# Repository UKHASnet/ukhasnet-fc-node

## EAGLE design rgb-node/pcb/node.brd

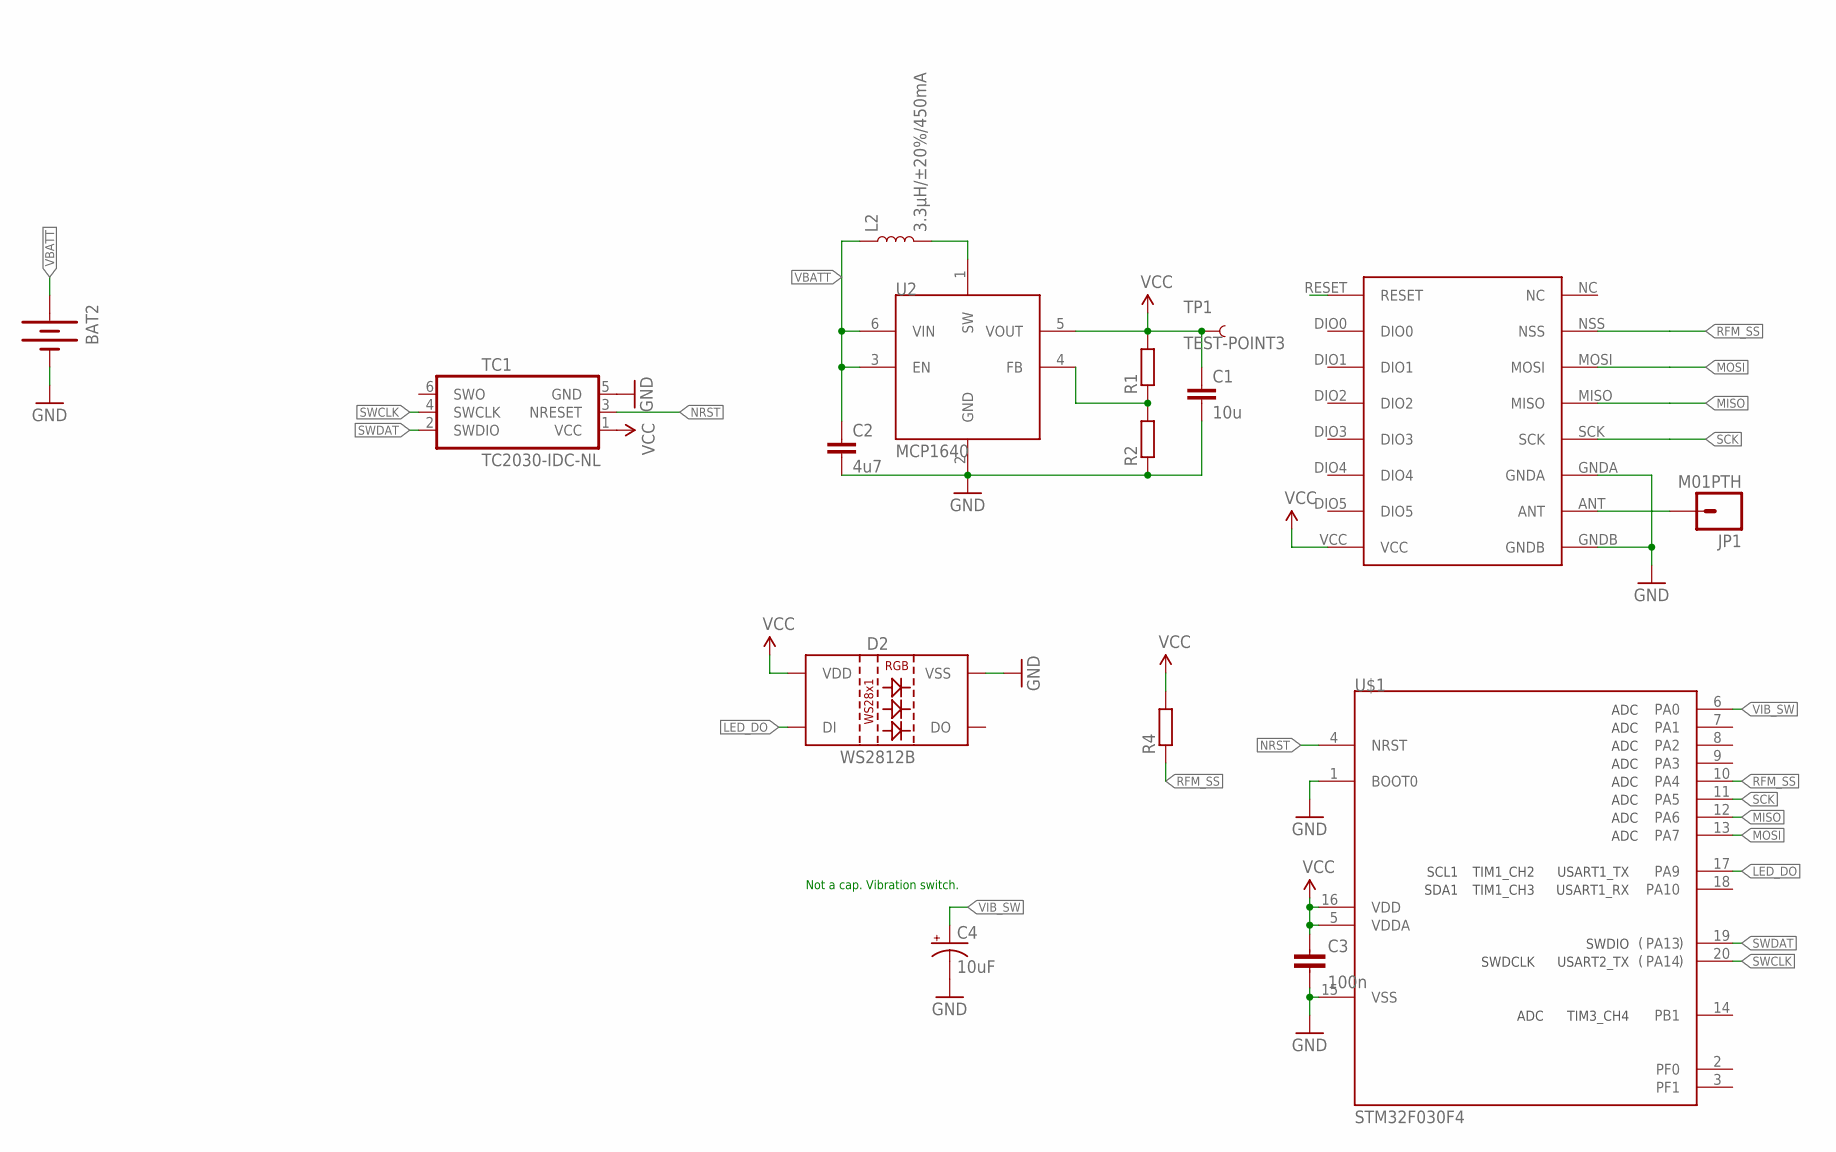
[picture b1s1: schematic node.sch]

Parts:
BAT2: BATTERYAA; BATTERY-AA
C1: 10u; C0603
C2: 4u7; C0603
C3: 100n; C0603-N
C4: 10uF; CPOL-RADIAL-2.5MM-5MM
D2: WS2812B
JP1: M01PTH; 1X01
L2: 3.3µH/±20%/450mA; 0805
R1, R2, R4: R-EU_R0603; R0603
TC1: TC2030-IDC-NL
TP1: TEST-POINT3; PAD.03X.03
U2: MCP1640; SOT23-6
U$1: STM32F030F4; TSSOP20
U$4: RFM69HW; RFM

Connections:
GND: BAT2.GND@1 (-), C1.2, C2.2, C3.2, C4.2 (-), D2.3 (VSS), R2.1, TC1.5 (GND), U2.2 (GND), U$1.1 (BOOT0), U$1.15 (VSS), U$4.GNDA, U$4.GNDB
LED_DO: D2.4 (DI), U$1.17 (PA9)
MISO: U$1.12 (PA6), U$4.MISO
MOSI: U$1.13 (PA7), U$4.MOSI
unnamed: L2.2, U2.1 (SW)
unnamed: R1.1, R2.2, U2.4 (FB)
unnamed: JP1.1, U$4.ANT
NRST: TC1.3 (NRESET), U$1.4 (NRST)
RFM_SS: R4.1, U$1.10 (PA4), U$4.NSS
SCK: U$1.11 (PA5), U$4.SCK
SWCLK: TC1.4 (SWCLK), U$1.20 (PA14)
SWDAT: TC1.2 (SWDIO), U$1.19 (PA13)
VBATT: BAT2.PWR@1 (+), C2.1, L2.1, U2.3 (EN), U2.6 (VIN)
VCC: C1.1, C3.1, D2.1 (VDD), R1.2, R4.2, TC1.1 (VCC), TP1.P$1, U2.5 (VOUT), U$1.5 (VDDA), U$1.16 (VDD), U$4.VCC
VIB_SW: C4.1 (+), U$1.6 (PA0)

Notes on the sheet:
Not a cap. Vibration switch.

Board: 2 copper layers, 16 parts (1 on the bottom side), 15 nets, no tracks yet.

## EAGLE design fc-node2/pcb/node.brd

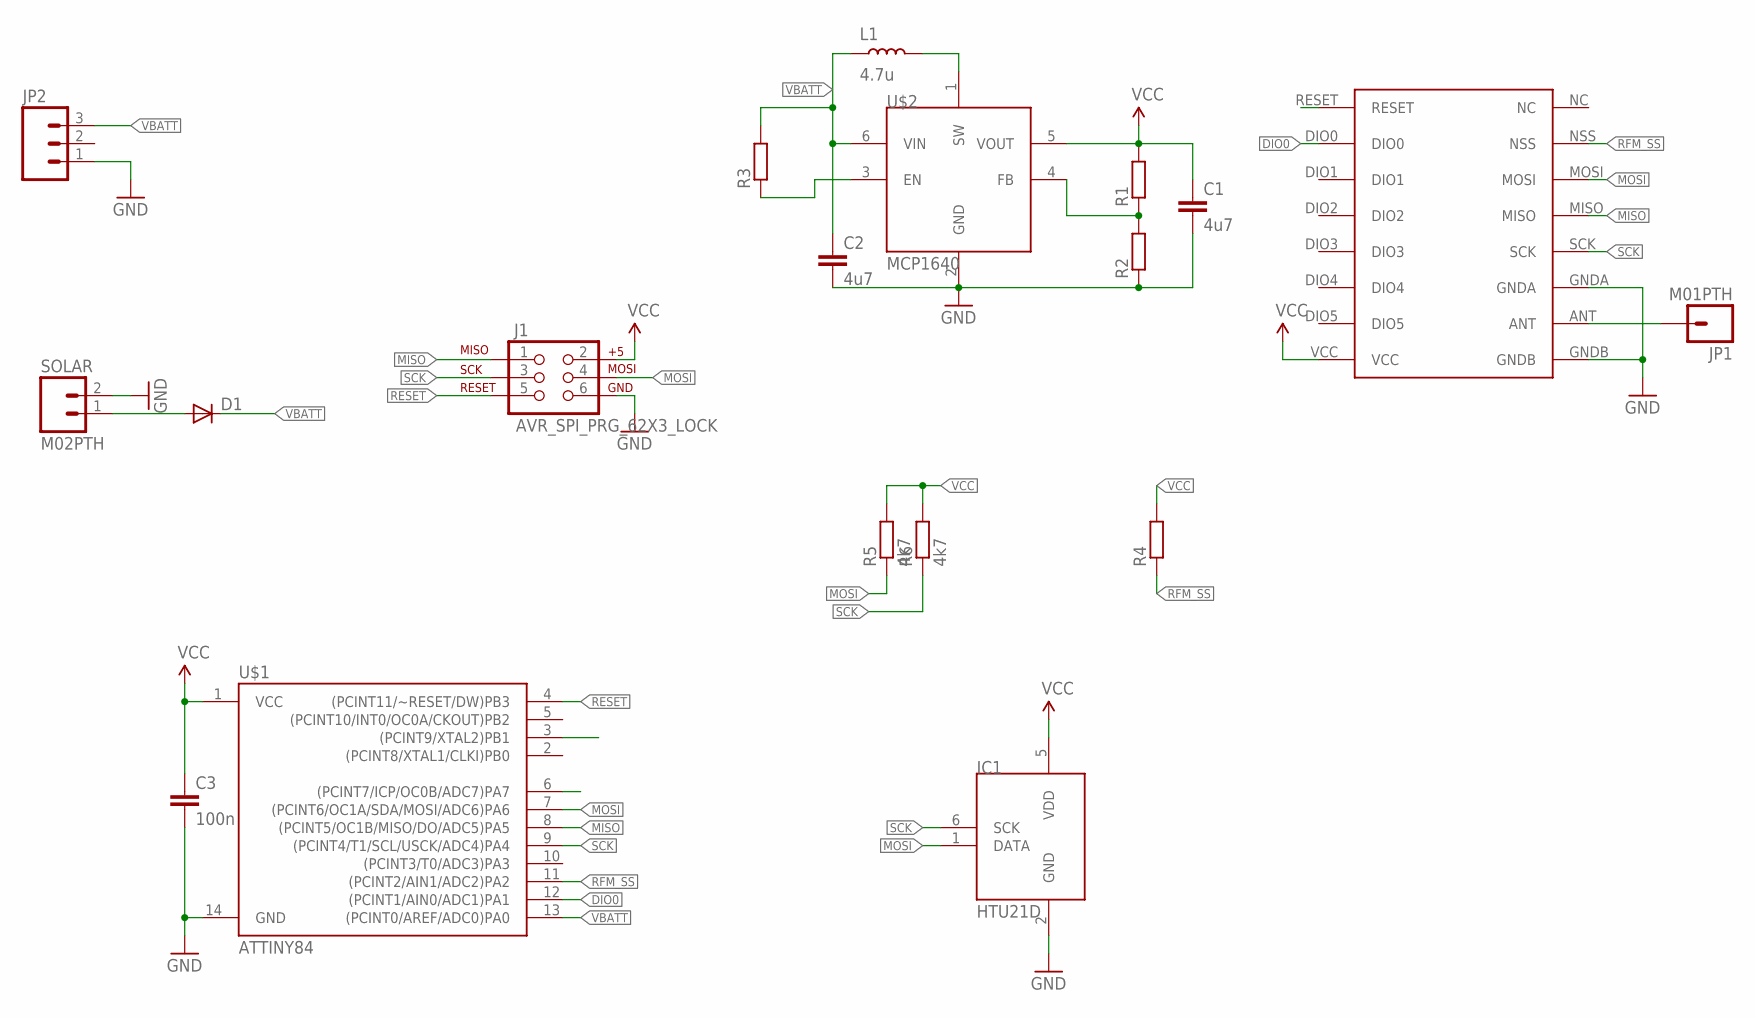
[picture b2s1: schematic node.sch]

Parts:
C1, C2: 4u7; C0603
C3: 100n; C0603
D1: DIODE-SOD123; SOD123
IC1: HTU21D; DFN6-L
J1: AVR_SPI_PRG_62X3_LOCK; 2X3_LOCK
JP1: M01PTH; 1X01
JP2: M03PTH; 1X03
L1: 4.7u; L0603-N
R1, R2, R3, R4: R-EU_R0603; R0603
R5, R6: 4k7; R0603
SOLAR: M02PTH; 1X02
U$1: ATTINY84; SO14
U$2: MCP1640; SOT23-6
U$4: RFM69HW; RFM

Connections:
DIO0: U$1.12 ((PCINT1/AIN0/ADC1)PA1), U$4.DIO0
EN: R3.1, U$2.3 (EN)
GND: C1.2, C2.2, C3.2, IC1.2 (GND), J1.6, JP2.1, R2.1, SOLAR.2, U$1.14 (GND), U$2.2 (GND), U$4.GNDA, U$4.GNDB
MISO: J1.1, U$1.8 ((PCINT5/OC1B/MISO/DO/ADC5)PA5), U$4.MISO
MOSI: IC1.1 (DATA), J1.4, R5.1, U$1.7 ((PCINT6/OC1A/SDA/MOSI/ADC6)PA6), U$4.MOSI
unnamed: L1.2, U$2.1 (SW)
unnamed: R1.1, R2.2, U$2.4 (FB)
unnamed: JP1.1, U$4.ANT
unnamed: D1.A, SOLAR.1
RESET: J1.5, U$1.4 ((PCINT11/~RESET/DW)PB3)
RFM_SS: R4.1, U$1.11 ((PCINT2/AIN1/ADC2)PA2), U$4.NSS
SCK: IC1.6 (SCK), J1.3, R6.1, U$1.9 ((PCINT4/T1/SCL/USCK/ADC4)PA4), U$4.SCK
VBATT: C2.1, D1.C, JP2.3, L1.1, R3.2, U$1.13 ((PCINT0/AREF/ADC0)PA0), U$2.6 (VIN)
VCC: C1.1, C3.1, IC1.5 (VDD), J1.2, R1.2, R4.2, R5.2, R6.2, U$1.1 (VCC), U$2.5 (VOUT), U$4.VCC

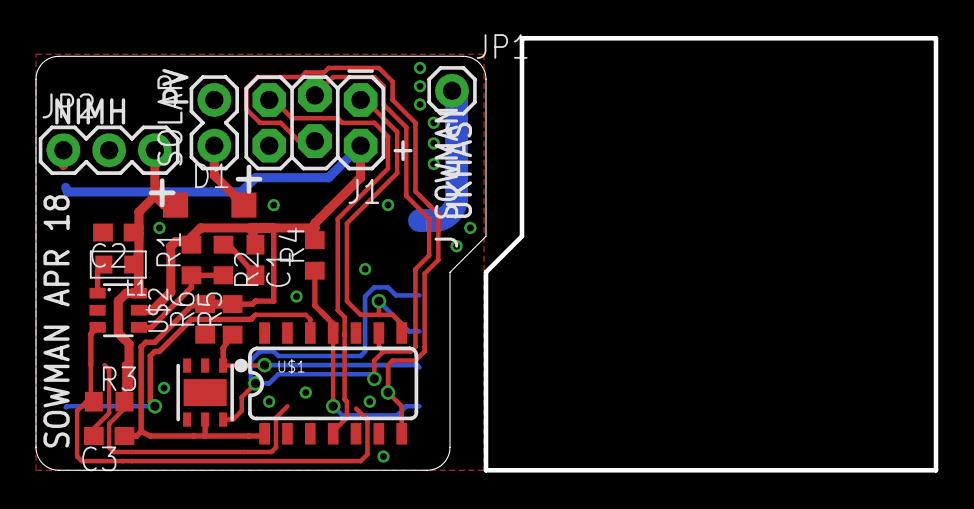
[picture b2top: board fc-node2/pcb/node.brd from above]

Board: 2 copper layers, 49.9 x 24.0 mm, 19 parts (1 on the bottom side), 14 nets.

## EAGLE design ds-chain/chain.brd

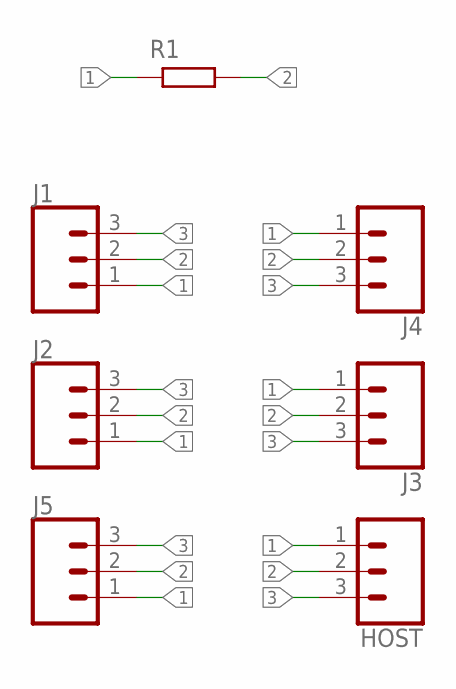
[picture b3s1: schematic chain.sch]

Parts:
HOST: CONN_03LONGPADS; 1X03_LONGPADS
J1, J2, J3, J4, J5: CONN_03LONGPADS; 1X03_LONGPADS
R1: RESISTOR0603-N; R0603-N

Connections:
1: HOST.1, J1.1, J2.1, J3.1, J4.1, J5.1, R1.1
2: HOST.2, J1.2, J2.2, J3.2, J4.2, J5.2, R1.2
3: HOST.3, J1.3, J2.3, J3.3, J4.3, J5.3

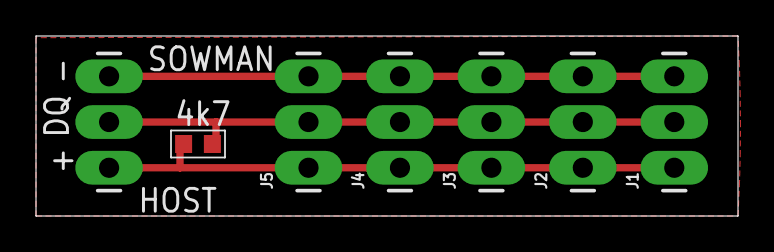
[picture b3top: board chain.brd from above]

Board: 2 copper layers, 39.0 x 10.0 mm, 7 parts (0 on the bottom side), 3 nets.

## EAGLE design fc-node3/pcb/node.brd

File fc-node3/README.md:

ds18b20 library is from
http://davidegironi.blogspot.co.uk/2014/09/a-ds18b20-1-wire-digital-thermometer.html

GPLv3

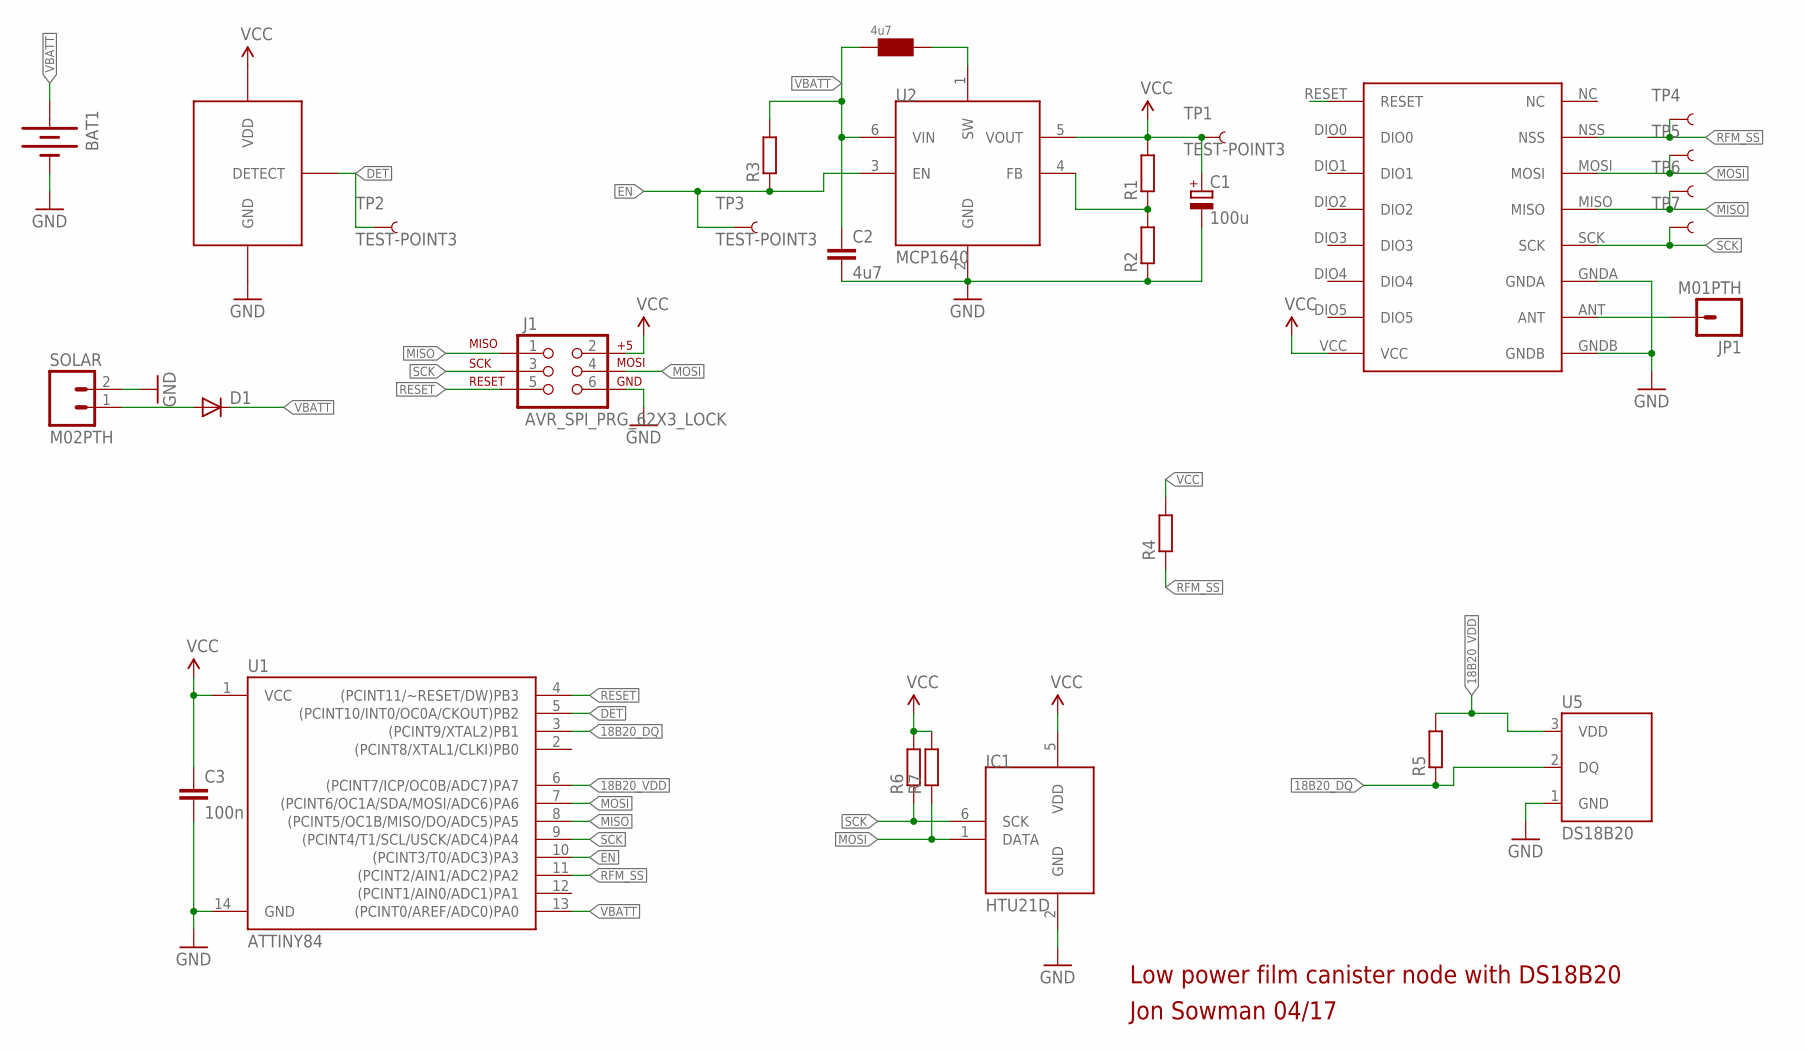
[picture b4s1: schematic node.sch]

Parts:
BAT1: BATTERYAAA; BATTERY-AAA
C1: 100u; SANYO-OSCON_SMD_C6
C2: 4u7; C0603
C3: 100n; C0603
D1: DIODE-SOD123; SOD123
DF: 4u7; BOURNS_SRN5040_L
IC1: HTU21D; DFN6-L
J1: AVR_SPI_PRG_62X3_LOCK; 2X3_LOCK
JP1: M01PTH; 1X01
R1, R2, R3, R4, R5, R6, R7: R-EU_R0603; R0603
SOLAR: M02PTH; 1X02
TP1, TP2, TP3, TP4, TP5, TP6, TP7: TEST-POINT3; PAD.03X.03
U1: ATTINY84; SO14
U2: MCP1640; SOT23-6
U3: BU49X_VDET_SOT235; SOT23-5L
U5: DS18B20; TO-92-AMMO
U$4: RFM69HW; RFM

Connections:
18B20_DQ: R5.1, U1.3 ((PCINT9/XTAL2)PB1), U5.2 (DQ)
18B20_VDD: R5.2, U1.6 ((PCINT7/ICP/OC0B/ADC7)PA7), U5.3 (VDD)
DET: TP2.P$1, U1.5 ((PCINT10/INT0/OC0A/CKOUT)PB2), U3.1 (DETECT)
EN: R3.1, TP3.P$1, U1.10 ((PCINT3/T0/ADC3)PA3), U2.3 (EN)
GND: BAT1.GND@1 (-), C1.-, C2.2, C3.2, IC1.2 (GND), J1.6, R2.1, SOLAR.2, U1.14 (GND), U2.2 (GND), U3.3 (GND), U5.1 (GND), U$4.GNDA, U$4.GNDB
MISO: J1.1, TP6.P$1, U1.8 ((PCINT5/OC1B/MISO/DO/ADC5)PA5), U$4.MISO
MOSI: IC1.1 (DATA), J1.4, R7.1, TP5.P$1, U1.7 ((PCINT6/OC1A/SDA/MOSI/ADC6)PA6), U$4.MOSI
unnamed: DF.P$2, U2.1 (SW)
unnamed: R1.1, R2.2, U2.4 (FB)
unnamed: JP1.1, U$4.ANT
unnamed: D1.A, SOLAR.1
RESET: J1.5, U1.4 ((PCINT11/~RESET/DW)PB3)
RFM_SS: R4.1, TP4.P$1, U1.11 ((PCINT2/AIN1/ADC2)PA2), U$4.NSS
SCK: IC1.6 (SCK), J1.3, R6.1, TP7.P$1, U1.9 ((PCINT4/T1/SCL/USCK/ADC4)PA4), U$4.SCK
VBATT: BAT1.PWR@1 (+), C2.1, D1.C, DF.P$1, R3.2, U1.13 ((PCINT0/AREF/ADC0)PA0), U2.6 (VIN)
VCC: C1.+, C3.1, IC1.5 (VDD), J1.2, R1.2, R4.2, R6.2, R7.2, TP1.P$1, U1.1 (VCC), U2.5 (VOUT), U3.2 (VDD), U$4.VCC

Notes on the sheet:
Low power film canister node with DS18B20
Jon Sowman 04/17

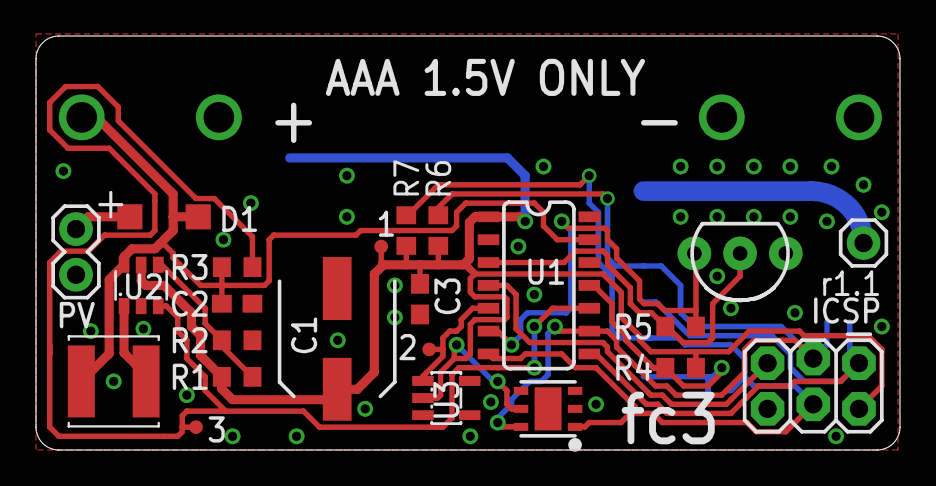
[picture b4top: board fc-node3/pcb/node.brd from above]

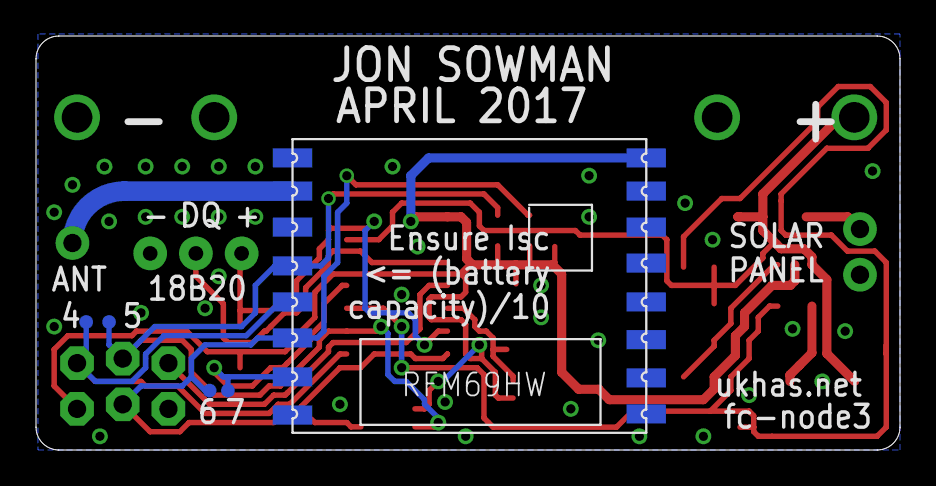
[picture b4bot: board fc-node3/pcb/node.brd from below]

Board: 2 copper layers, 48.0 x 23.0 mm, 29 parts (5 on the bottom side), 16 nets.

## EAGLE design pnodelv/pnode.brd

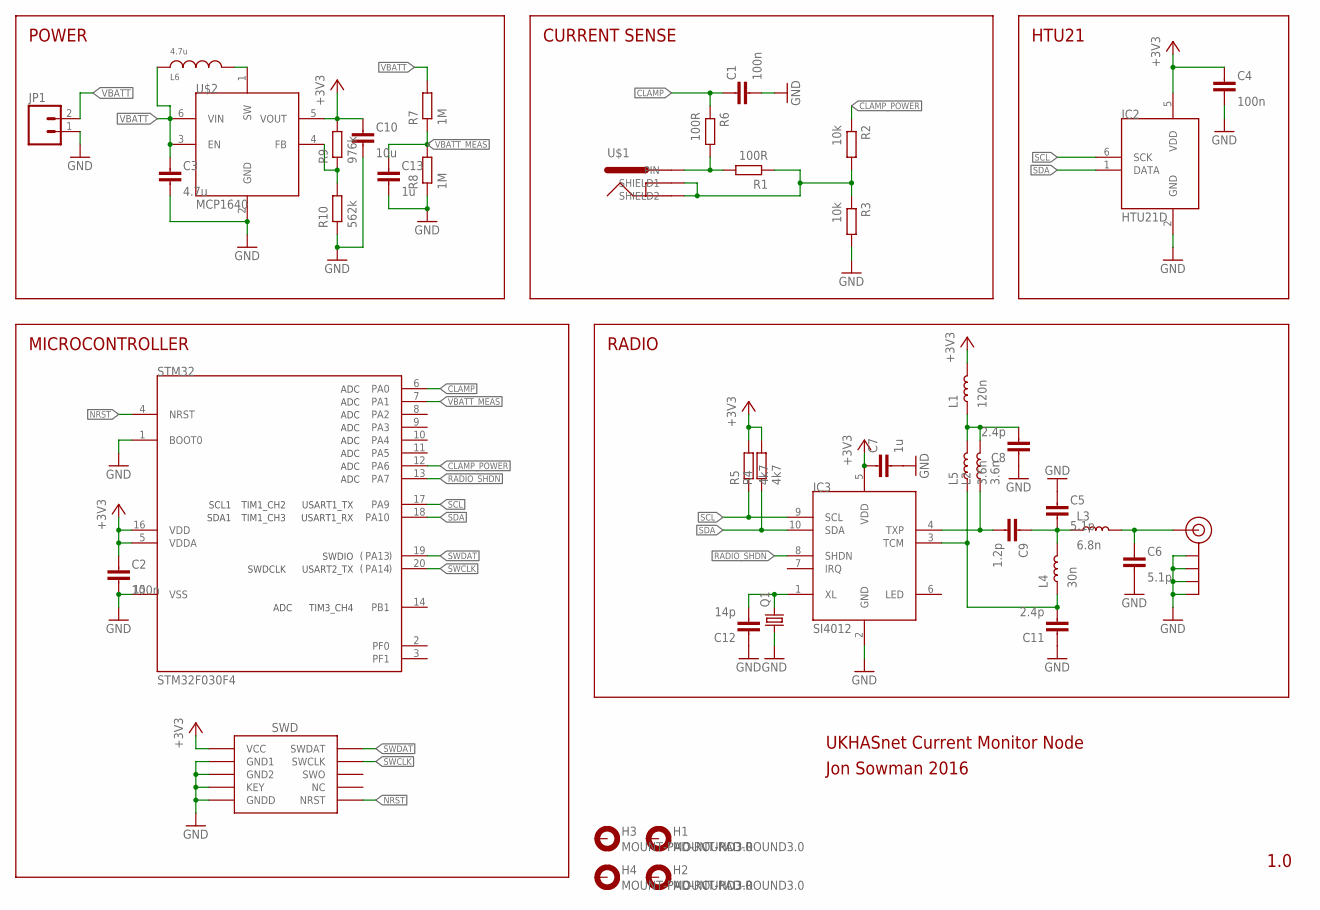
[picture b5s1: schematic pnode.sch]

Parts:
C1, C2, C4: 100n; C0603-N
C3: 4.7u; C0603-N
C5, C6: 5.1p; C0603-N
C7, C13: 1u; C0603-N
C8, C11: 2.4p; C0603-N
C9: 1.2p; C0603-N
C10: 10u; C0603-N
C12: 14p; C0603-N
H1, H2, H3, H4: MOUNT-PAD-ROUND3.0; 3,0-PAD
IC2: HTU21D; DFN6-L
IC3: SI4012; MSOP10
J1: SWD_SHROUD_SMD; SWD_SMD_SHROUD
J$1: SMA_EDGE; SMA-EDGE
JP1: M02PTH; 1X02
L1: 120n; L0603-N
L2, L5: 3.6n; L0402-N
L3: 6.8n; L0402-N
L4: 30n; L0402-N
L6: 4.7u; BOURNS_SDE0403A
Q1: CRYSTALHC49S; HC49/S
R1, R6: 100R; R0603-N
R2, R3: 10k; R0603-N
R4, R5: 4k7; R0603-N
R7, R8: 1M; R0603-N
R9: 976k; R0603-N
R10: 562k; R0603-N
STM32: STM32F030F4; TSSOP20
U$1: 13MM_DC_JACKPTH; 13MM_DC_JACK
U$2: MCP1640; SOT23-6

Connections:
+3V3: C2.1, C4.1, C7.1, C10.1, IC2.5 (VDD), IC3.5 (VDD), J1.1 (VCC), L1.2, R4.2, R5.2, R9.2, STM32.5 (VDDA), STM32.16 (VDD), U$2.5 (VOUT)
CLAMP: C1.1, R6.1, STM32.6 (PA0)
CLAMP_POWER: R2.1, STM32.12 (PA6)
GND: C1.2, C2.2, C3.2, C4.2, C5.1, C6.2, C7.2, C8.1, C10.2, C11.1, C12.1, C13.2, IC2.2 (GND), IC3.2 (GND), J1.3 (GND1), J1.5 (GND2), J1.7 (KEY), J1.9 (GNDD), J$1.GND@0 (GND), J$1.GND@1 (GND), J$1.GND@2 (GND), J$1.GND@3 (GND), JP1.1, Q1.1, R3.2, R8.1, R10.1, STM32.1 (BOOT0), STM32.15 (VSS), U$2.2 (GND)
unnamed: R1.2, R6.2, U$1.1 (PIN)
unnamed: R1.1, R2.2, R3.1, U$1.2 (SHIELD1), U$1.3 (SHIELD2)
unnamed: R9.1, R10.2, U$2.4 (FB)
unnamed: C8.2, L1.1, L2.2, L5.2
unnamed: C12.2, IC3.1 (XL), Q1.2
unnamed: L6.P$2, U$2.1 (SW)
unnamed: C5.2, C9.1, L3.1, L4.2
unnamed: C11.2, IC3.3 (TCM), L4.1, L5.1
unnamed: C9.2, IC3.4 (TXP), L2.1
unnamed: C6.1, J$1.SIG (SIGNAL), L3.2
NRST: J1.10 (NRST), STM32.4 (NRST)
RADIO_SHDN: IC3.8 (SHDN), STM32.13 (PA7)
SCL: IC2.6 (SCK), IC3.9 (SCL), R5.1, STM32.17 (PA9)
SDA: IC2.1 (DATA), IC3.10 (SDA), R4.1, STM32.18 (PA10)
SWCLK: J1.4 (SWCLK), STM32.20 (PA14)
SWDAT: J1.2 (SWDAT), STM32.19 (PA13)
VBATT: C3.1, JP1.2, L6.P$1, R7.2, U$2.3 (EN), U$2.6 (VIN)
VBATT_MEAS: C13.1, R7.1, R8.2, STM32.7 (PA1)

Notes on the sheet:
UKHASnet Current Monitor Node
Jon Sowman 2016
1.0
POWER
CURRENT SENSE
RADIO
MICROCONTROLLER
HTU21

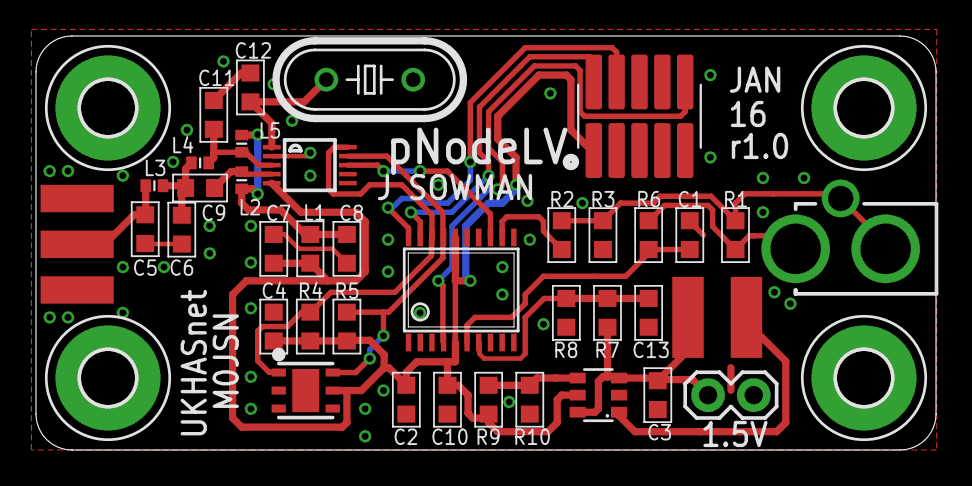
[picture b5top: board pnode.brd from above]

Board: 2 copper layers, 50.0 x 23.0 mm, 42 parts (0 on the bottom side), 22 nets.

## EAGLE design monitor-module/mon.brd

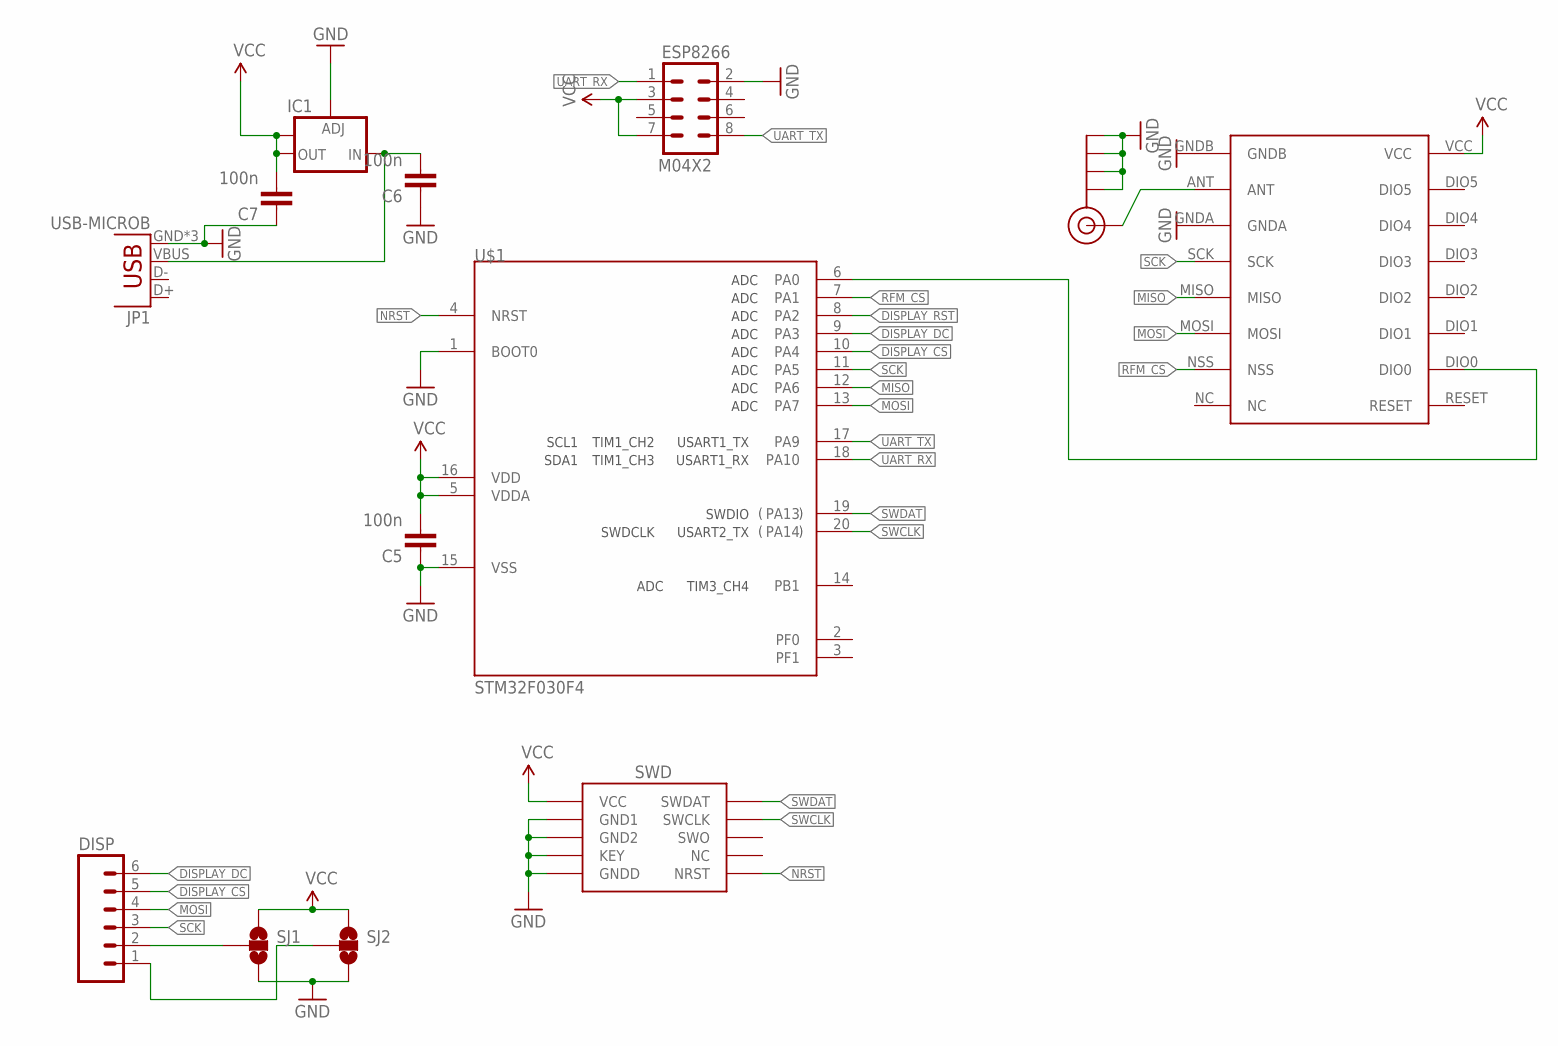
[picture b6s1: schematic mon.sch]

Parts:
C5, C6, C7: 100n; C0603-L
DISP: M06SILK_FEMALE_PTH; 1X06
ESP8266: M04X2; 2X4
IC1: V_REG_LM1117SOT223; SOT223
J$1: SMA_EDGE; SMA-EDGE
JP1: USB-MICROB
SJ1, SJ2: SOLDERJUMPER_2WAYS; SJ_3
U$1: STM32F030F4; TSSOP20
U$2: RFM69HW; RFM
U$4: SWD_SHROUD_SMD; SWD_SMD_SHROUD

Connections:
DISPLAY_CS: DISP.5, U$1.10 (PA4)
DISPLAY_DC: DISP.6, U$1.9 (PA3)
DISPLAY_RST: U$1.8 (PA2)
GND: C5.1, C6.1, C7.1, ESP8266.2, IC1.1 (ADJ), J$1.GND@0 (GND), J$1.GND@1 (GND), J$1.GND@2 (GND), J$1.GND@3 (GND), JP1.GND, JP1.MT1 (GND), JP1.MT2 (GND), SJ1.3, SJ2.3, U$1.1 (BOOT0), U$1.15 (VSS), U$2.GNDA, U$2.GNDB, U$4.3 (GND1), U$4.5 (GND2), U$4.7 (KEY), U$4.9 (GNDD)
MISO: U$1.12 (PA6), U$2.MISO
MOSI: DISP.4, U$1.13 (PA7), U$2.MOSI
unnamed: J$1.SIG (SIGNAL), U$2.ANT
unnamed: C6.2, IC1.3 (IN), JP1.VBUS
unnamed: U$1.6 (PA0), U$2.DIO0
unnamed: DISP.2, SJ1.2
unnamed: DISP.1, SJ2.2
NRST: U$1.4 (NRST), U$4.10 (NRST)
RFM_CS: U$1.7 (PA1), U$2.NSS
SCK: DISP.3, U$1.11 (PA5), U$2.SCK
SWCLK: U$1.20 (PA14), U$4.4 (SWCLK)
SWDAT: U$1.19 (PA13), U$4.2 (SWDAT)
UART_RX: ESP8266.1, U$1.18 (PA10)
UART_TX: ESP8266.8, U$1.17 (PA9)
VCC: C5.2, C7.2, ESP8266.3, ESP8266.7, IC1.2 (OUT), IC1.4 (OUT), SJ1.1, SJ2.1, U$1.5 (VDDA), U$1.16 (VDD), U$2.VCC, U$4.1 (VCC)

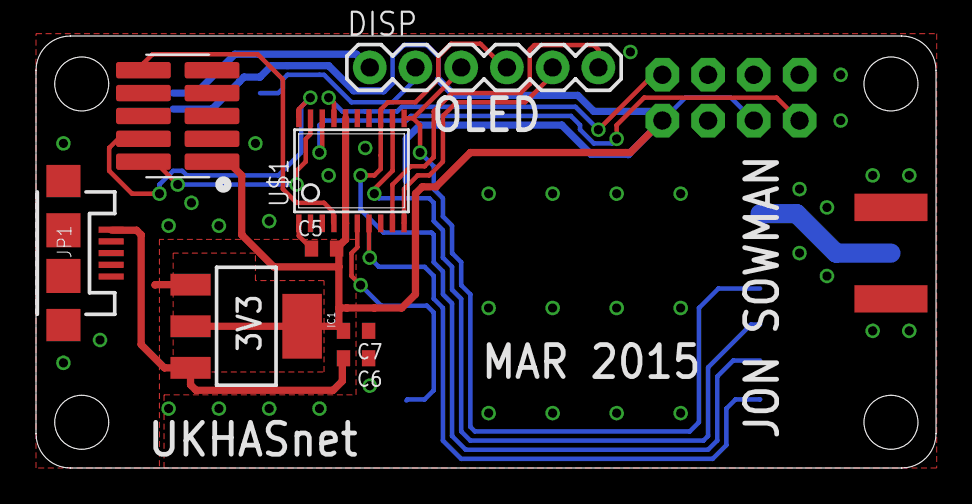
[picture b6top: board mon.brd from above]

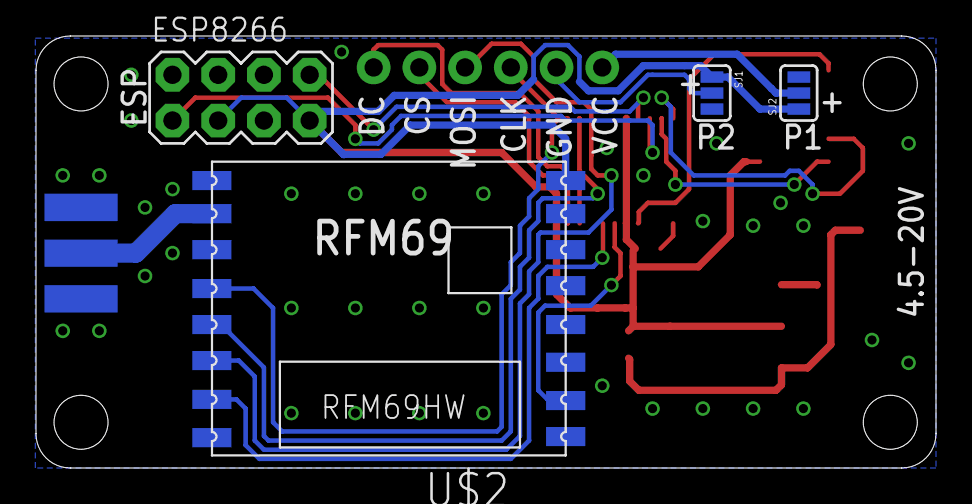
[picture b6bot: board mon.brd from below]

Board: 2 copper layers, 50.0 x 24.0 mm, 13 parts (5 on the bottom side), 18 nets.

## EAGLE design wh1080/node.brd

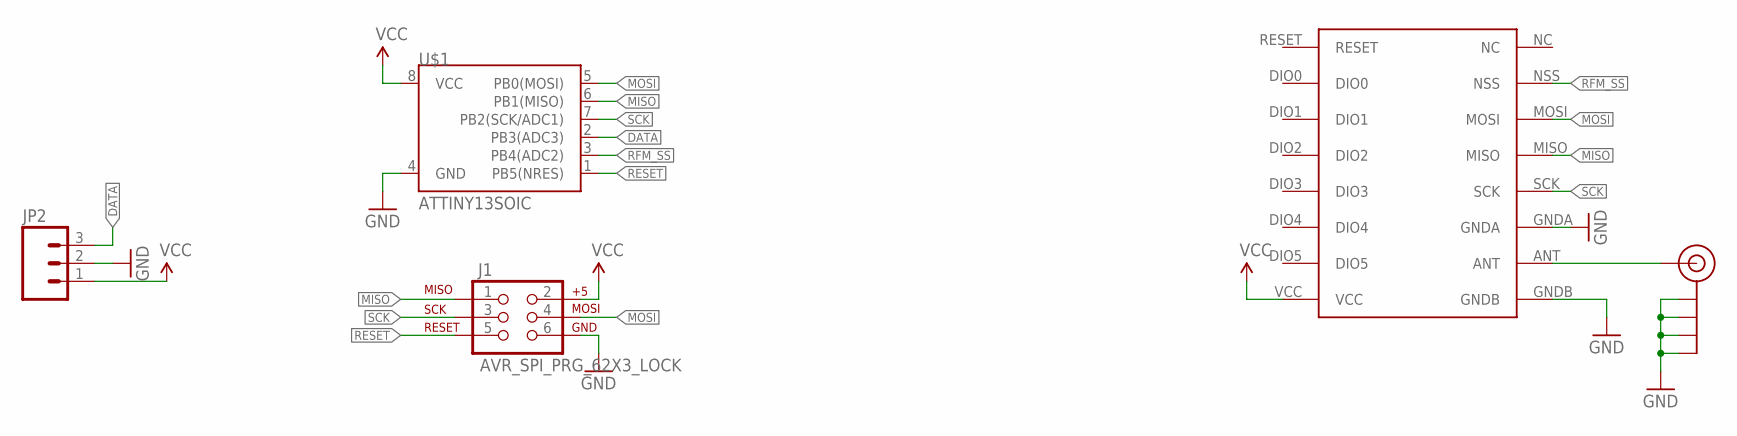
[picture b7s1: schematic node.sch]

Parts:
J1: AVR_SPI_PRG_62X3_LOCK; 2X3_LOCK
J$1: SMA_EDGE; SMA-EDGE
JP2: M03PTH; 1X03
U$1: ATTINY13SOIC; SO08
U$4: RFM69HW; RFM

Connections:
DATA: JP2.3, U$1.2 (PB3(ADC3))
GND: J1.6, J$1.GND@0 (GND), J$1.GND@1 (GND), J$1.GND@2 (GND), J$1.GND@3 (GND), JP2.2, U$1.4 (GND), U$4.GNDA, U$4.GNDB
MISO: J1.1, U$1.6 (PB1(MISO)), U$4.MISO
MOSI: J1.4, U$1.5 (PB0(MOSI)), U$4.MOSI
unnamed: J$1.SIG (SIGNAL), U$4.ANT
RESET: J1.5, U$1.1 (PB5(NRES))
RFM_SS: U$1.3 (PB4(ADC2)), U$4.NSS
SCK: J1.3, U$1.7 (PB2(SCK/ADC1)), U$4.SCK
VCC: J1.2, JP2.1, U$1.8 (VCC), U$4.VCC

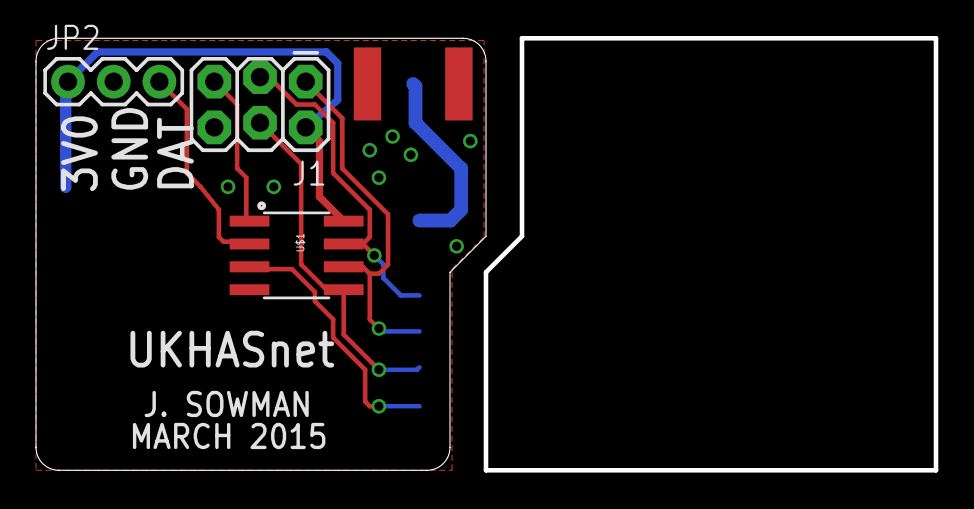
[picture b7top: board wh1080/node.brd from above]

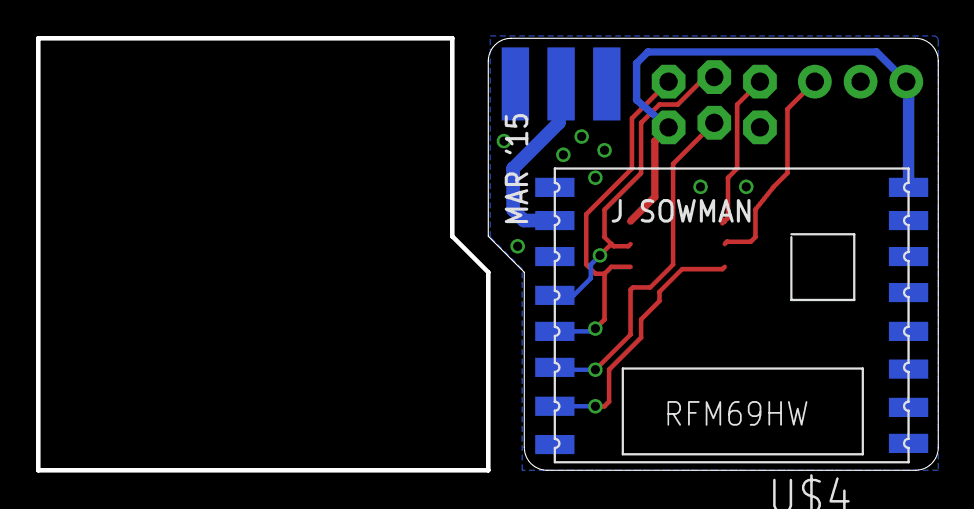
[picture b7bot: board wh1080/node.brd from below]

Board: 2 copper layers, 49.9 x 24.0 mm, 5 parts (2 on the bottom side), 9 nets.

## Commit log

2015-01-25 Delta-u (change in input) constraints are working
2015-01-26 placing parts
2015-01-28 routing commence
2015-03-12 finished routing fc node
2015-03-13 added wh1080 ukhasnet transmitter
2015-03-21 monitor
2015-03-21 monitor done
2015-03-21 tidying mon
2015-03-22 routed wh1080 txer
2015-03-23 screen module version of monitor
2015-03-23 submitted
2015-03-23 added jumpers because dont trust ebay sellers
2015-03-23 removed central routing island
2015-03-24 tied reset line high (in panelised only)
2015-04-02 reduced to 23mm, begin routing fc2
2015-04-02 routed fc2
2015-04-03 fc2 decoupling cap
2015-08-14 fc2 pcb running
2015-08-14 testing boost reg
2015-08-14 fc2 running ok, no rfm yet
2015-08-16 Work on bitbanged firmware for a attiny node
2015-08-16 SPI rx doesn't seem to be working
2015-08-16 Fixed a stupid
2015-08-16 Think it's working... bedtime
2015-08-16 Sleepy
2015-08-17 working sending dummy packets
2015-08-17 Working powering off boost reg during sleep stages
2015-08-17 Fixed a mistyped signal handler causing reset
2015-08-17 Fixed delays back to something minimal
2015-08-18 Working ADC and voltage transmission
2015-08-27 wake less often
2015-08-27 wake less often 2
2015-08-28 enable 1v8 brown out
2015-08-28 disable 1v8 brown out
2015-09-02 added potential divider for vbatt so we can use internal 1v1 ref
2015-09-02 put things in the right places
2016-01-28 Current clamp board
2016-01-28 routing pnode
2016-01-28 Routing and tidying + silk
2016-01-28 Tidying up silk
2016-01-29 1.5v pnode
2016-01-29 Routing for pnodelv
2016-01-29 Added silk and submitted gerbers for pnodelv
2016-01-29 switched to smd swd header
2016-01-31 tidying silk again
2016-04-06 restructure
2016-04-06 Chibios
2016-04-06 er what
2016-04-06 chibi
2016-04-06 chibi init nil
2016-04-06 removed unwanted thing
2016-04-06 ignore chibi builds
2016-04-06 use i2c1, don't use serial, 2 threads is fine
2016-04-06 unhandled exception still happening
2016-04-06 added board
2016-04-06 all IO to default
2016-04-06 single thread
2016-04-06 syntastic
2016-04-06 syntastic nil
2016-04-06 use 16 bit timer 3 for systick
2016-04-07 start i2c work
2016-04-08 i2c working
2016-04-08 use stm32 internal pullups
2016-04-08 keep radio out of shdn
2016-04-10 radio responds over i2c
2016-04-10 Use separate i2cmasterreceive to force a STOP after the command bytes
2016-09-25 new fc node
2016-09-26 routed fc3
2016-09-26 tidying
2016-09-26 nicey silky
2016-09-26 tidying routing for fc3
2016-09-27 labelling 18b20 pins
2016-09-27 power ds18b20 from avr pin
2016-09-27 gc-sections
2016-09-27 makefile tidying
2016-10-15 pullups i2c on fc3
2016-10-15 firmware for fc3
2016-10-15 using pa1/2
2016-10-15 use pa1 only 10dbm
2016-10-15 20mW, PA1+2
2016-10-16 new rfm, use pa1 only
2016-10-16 tidying code for fc3
2016-10-22 configurable tx power
2016-10-26 optional wdt mode
2017-03-22 rfm69 timeout on pa ramp and packet-sent
2017-04-05 layout for fc3 r1.1
2017-04-09 HARDWARE: isp pogo
2017-04-09 panel2 for r1.1 of fc3 and ispogo
2018-02-18 rgb node attempt 1
2018-02-18 dumped some things on the pcb
2018-02-18 dumped some things on the pcb 12
2018-02-25 negative temperature library bug fixed
2018-02-25 using itoa/utoa to save on flash
2018-03-04 fall back to wdt once the cell voltage falls below a certain value. this should give longer runtimes on alkaline cells
2018-03-13 adapt fc2 to take 80mah nimh button cells with solder tabs
2018-03-18 commiting work on rgb-node

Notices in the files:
parts and their libraries:
SparkFun-Connectors: Licensing: Creative Commons ShareAlike 4.0 International - https://creativecommons.org/licenses/by-sa/4.0
SparkFun: Licensing: CC v3.0 Share-Alike You are welcome to use this library for commercial purposes.
